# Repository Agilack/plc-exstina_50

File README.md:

# plc-exstina_50
ExStina programmable logic controller

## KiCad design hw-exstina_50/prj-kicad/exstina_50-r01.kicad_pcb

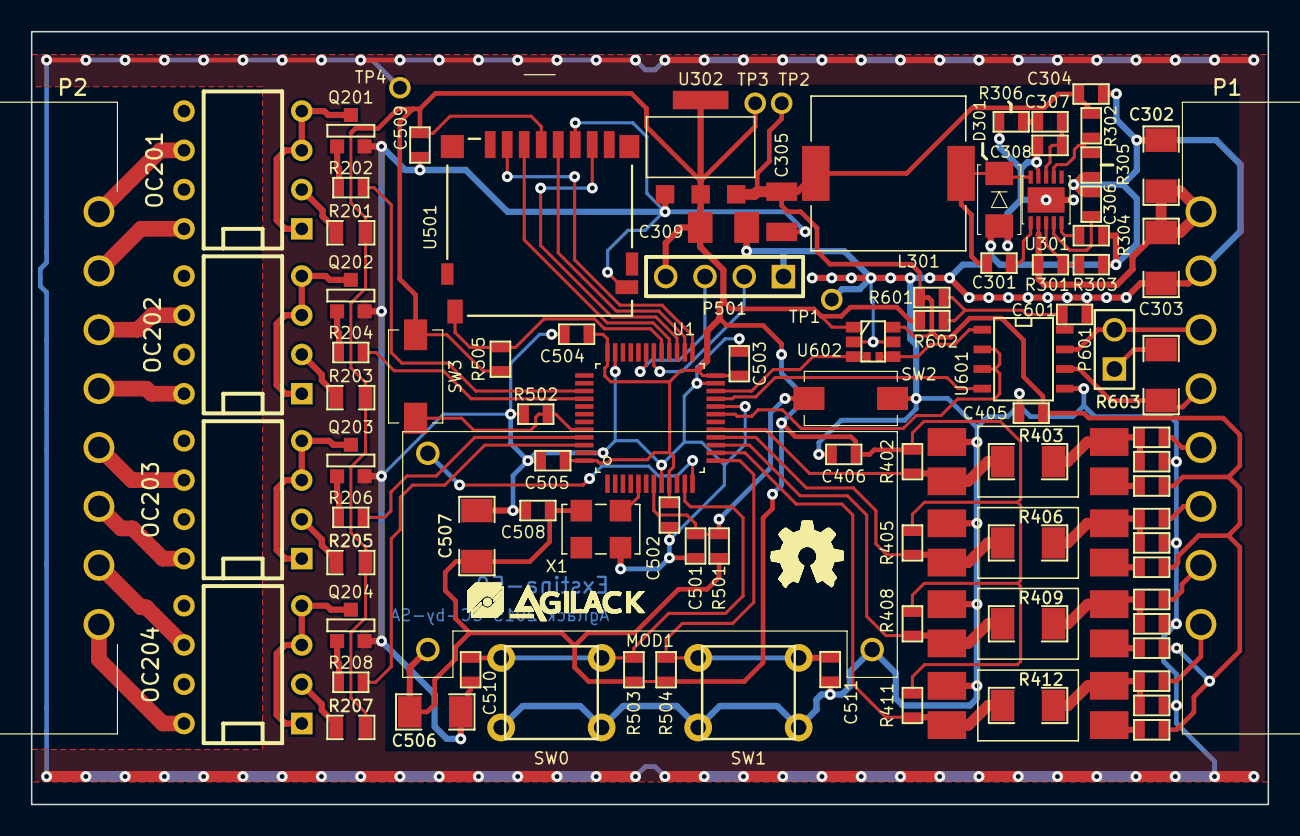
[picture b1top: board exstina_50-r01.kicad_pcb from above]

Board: 2 copper layers, 80.0 x 50.0 mm, 102 parts (0 on the bottom side), 73 nets.

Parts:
C301, C406, C502, C503, C504, C505, C508, C509, C601: 100nF; SMD0603
C302, C303: 10uF; SMD1206
C304, C405, C501, C510, C511: 1uF; SMD0603
C305, C309: 47uF; C_TAJB
C306: 10nF; SMD0603
C307: 180pF; SMD0603
C308: 10Pf; SMD0603
C401, C402, C403, C404: C; SMD0603
C506, C507: 2,2uF; SMD1206
D301: B160; DO214-AC
FB401, FB402, FB403, FB404: FB1000; SMD0603
L301: 47uH; I_MSS1048
MOD1: MOD_DISP
OC201, OC202, OC203, OC204: AQHX213; DIP-8__300
P1, P2: CONN_8; CONN-691701350008B
P501: CONN_4
P601: JUMPER; CONN_2
Q201, Q202, Q203, Q204: T_NPN; SOT23-3
R201, R203, R205, R207: 165; SMD0805
R202, R204, R206, R208, R402, R405, R408, R411, R501, R502, R503, R504, R505: 10k; SMD0603
R301, R304: 100k; SMD0603
R302, R305: R; SMD0603
R303: 48.7k; SMD0603
R306: 75K; SMD0603
R401, R404, R407, R410: 470; SMD0603
R403, R406, R409, R412: 0; SMD1206
R601, R602: 0; SMD0603
R603: 120; SMD1206
R604: 0; SMD0402
SW0, SW1: SW_PUSH; SW_FSM2JH
SW2, SW3: SW_PUSH; SW_434123043816
TP1, TP2, TP3, TP4: CONN_1; TP_PIN
U1: STM32F103CX; LQFP48
U301: TPS54060; SMD_SON10
U302: LDO_1117-3.3; SOT223
U401: VO615; VO615A
U402, U403, U404: OPTO-TRANSISTOR; VO615A
U501: CONN_USD; CONN_114-00841-68
U601: SN65HVD1785; SMD_SO8E
U602: SN74LVC1T45; SOT23-6
X1: 8MHz; Q_SMD5x3
agilack-11.5: 450px; agilack-11.5
ohw_logo: VAL**; ohw-logo

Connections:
+3.3V: C309.1, C406.1, C502.1, C503.1, C504.1, C505.1, C506.1, C507.1, C508.1, C509.1, MOD1.3, P501.4, R201.1, R203.1, R205.1, R207.1, R402.1, R405.1, R408.1, R411.1, R501.2, R503.1, R504.1, R505.1, R602.1, SW3.1, TP3.1, U1.9, U1.24, U1.36, U1.48, U302.2, U302.4, U501.4, U602.1, X1.4
+5V: C304.1, C305.1, C405.1, L301.2, R302.1, R401.2, R404.2, R407.2, R410.2, R601.1, TP2.1, U302.3, U602.6
BOOT: R502.2, SW3.2, U1.44
COMM_1: P1.6, P601.2, U601.7
COMM_2: P1.5, R603.1, U601.6
COMM_IO: U1.19, U601.2, U601.3
DBG_RX: P501.3, U1.31
DBG_TX: P501.2, U1.30
DISP_DAT: MOD1.2, U1.12
EXT-IN-1: FB401.1, P1.4
EXT-IN-2: FB402.1, P1.3
EXT-IN-3: FB403.1, P1.2
EXT-IN-4: FB404.1, P1.1
IN-1: R402.2, R403.2, U1.17, U401.4
IN-2: R405.2, R406.2, U1.16, U402.4
IN-3: R408.2, R409.2, U1.15, U403.4
IN-4: R411.2, R412.2, U1.14, U404.4
MAIN_OSC: U1.5, X1.3
unnamed: OC202.1, OC202.3, OC202.4, Q202.3
unnamed: Q202.1, R204.2
unnamed: OC201.1, OC201.3, OC201.4, Q201.3
unnamed: Q201.1, R202.2
unnamed: OC204.1, OC204.3, OC204.4, Q204.3
unnamed: Q204.1, R208.2
unnamed: OC203.1, OC203.3, OC203.4, Q203.3
unnamed: Q203.1, R206.2
unnamed: OC202.2, R203.2
unnamed: OC203.2, R205.2
unnamed: OC204.2, R207.2
unnamed: OC201.2, R201.2
unnamed: R302.2, R305.1, U301.7
unnamed: C307.1, C308.1, U301.8
unnamed: C307.2, R306.1
unnamed: C301.1, U301.1
unnamed: C301.2, D301.2, L301.1, U301.10
unnamed: R301.2, R303.1, U301.3
unnamed: C306.1, U301.4
unnamed: R304.1, U301.5
unnamed: C404.1, FB404.2, R412.1, U404.2
unnamed: C403.1, FB403.2, R409.1, U403.2
unnamed: R407.1, U403.1
unnamed: R410.1, U404.1
unnamed: C401.1, FB401.2, R403.1, U401.2
unnamed: R401.1, U401.1
unnamed: C402.1, FB402.2, R406.1, U402.2
unnamed: R404.1, U402.1
unnamed: C601.1, R601.2, R602.2, U601.8
unnamed: R604.1, U601.1, U602.4
unnamed: P601.1, R603.2
OUT1: R202.1, U1.39
OUT1-1: OC201.6, P2.1
OUT1-2: OC201.8, P2.2
OUT2: R204.1, U1.40
OUT2-1: OC202.6, P2.3
OUT2-2: OC202.8, P2.4
OUT3: R206.1, U1.45
OUT3-1: OC203.6, P2.5
OUT3-2: OC203.8, P2.6
OUT4: R208.1, U1.46
OUT4-1: OC204.6, P2.7
OUT4-2: OC204.8, P2.8
PWR_V+: C302.1, C303.1, P1.8, R301.1, U301.2
PWR_V-: C302.2, C303.2, C304.2, C305.2, C306.2, C308.2, C309.2, C401.2, C402.2, C403.2, C404.2, C405.2, C406.2, C501.2, C502.2, C503.2, C504.2, C505.2, C506.2, C507.2, C508.2, C509.2, C510.2, C511.2, C601.2, D301.1, MOD1.1, P1.7, P501.1, Q201.2, Q202.2, Q203.2, Q204.2, R303.2, R304.2, R305.2, R306.2, R502.1, SW0.1, SW1.1, SW2.1, TP1.1, TP4.1, U1.8, U1.20, U1.23, U1.35, U1.47, U301.9, U301.PAD, U302.1, U401.3, U402.3, U403.3, U404.3, U501.6, U501.CD1, U601.5, U602.2, U602.5, X1.2
RST: C501.1, R501.1, SW2.2, U1.7
SD_DETECT: R505.2, U1.29, U501.CD2
SPI2_MISO: U1.27, U501.7
SPI2_MOSI: U1.28, U501.3
SPI2_NSS: U1.25, U501.2
SPI2_SCK: U1.26, U501.5
SW0: C510.1, R503.2, SW0.2, U1.11
SW1: C511.1, R504.2, SW1.2, U1.13
UART3_RX: R604.2, U1.22, U602.3
UART3_TX: U1.21, U601.4

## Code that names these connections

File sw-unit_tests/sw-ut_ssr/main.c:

/**
 * Exstina-50 - Outputs unit-test
 *
 * Copyright (c) 2015 Saint-Genest Gwenael <gwen@agilack.fr>
 *
 * This file may be distributed and/or modified under the terms of the
 * GNU General Public License version 2 as published by the Free Software
 * Foundation. (See COPYING.GPL for details.)
 *
 * This file is provided AS IS with NO WARRANTY OF ANY KIND, INCLUDING THE
 * WARRANTY OF DESIGN, MERCHANTABILITY AND FITNESS FOR A PARTICULAR PURPOSE.
 *
 */
#include "hardware.h"
#include "main.h"
#include "uart.h"
#include "display.h"
#include "output.h"

void serial_menu(void);
void disp_menu  (void);
static int but_value(void);

int menu_sel;

int main(void)
{
    int c;

    hw_init();
    uart_init();
    
    hw_out_init();
    
    uart_puts("Exstina-50 - Outputs Unit Test\r\n");
    uart_crlf();
    
    disp_init();
    disp_puts(3, "Outputs Test 0.1");
    
    menu_sel = 0;
    
    while(1)
    {
        serial_menu();
        disp_menu();
        while ( ( ! uart_isready()) && (but_value() == 0) )
            ;
        
        if (but_value() != 0)
        {
            /* If left button has been pressed */
            if (but_value() & 2)
            {
                menu_sel++;
                if (menu_sel == 5)
                    menu_sel = 1;
            }
            /* If right button has been pressed  */
            else if (but_value() & 8)
            {
                switch(menu_sel)
                {
                    case 1:
                        out_toggle(OUT_1);
                        break;
                    case 2:
                        out_toggle(OUT_2);
                        break;
                    case 3:
                        out_toggle(OUT_3);
                        break;
                    case 4:
                        out_toggle(OUT_4);
                        break;
                }
            }
            /* Wait until all button released */
            while( but_value() )
                ;
            continue;
        }
        
        c = uart_rd();
        switch(c)
        {
            case 'a':
                uart_puts("Set ALL SSR ON\r\n");
                out_set(OUT_1, OUT_ON);
                out_set(OUT_2, OUT_ON);
                out_set(OUT_3, OUT_ON);
                out_set(OUT_4, OUT_ON);
                break;
                
            case 'n':
                uart_puts("Set ALL SSR OFF\r\n");
                out_set(OUT_1, OUT_OFF);
                out_set(OUT_2, OUT_OFF);
                out_set(OUT_3, OUT_OFF);
                out_set(OUT_4, OUT_OFF);
                break;
                
            case '1':
                uart_puts("Set SSR-1 ");
                /* Invert the output 1 state */
                out_toggle(OUT_1);
                /* Send new state to debug port */
                if (out_status(OUT_1) == OUT_ON)
                    uart_puts("ON\r\n");
                else
                    uart_puts("OFF\r\n");
                break;
                
            case '2':
                uart_puts("Set SSR-2 ");
                /* Invert the output 2 state */
                out_toggle(OUT_2);
                /* Send new state to debug port */
                if (out_status(OUT_2) == OUT_ON)
                    uart_puts("ON\r\n");
                else
                    uart_puts("OFF\r\n");
                break;
                
            case '3':
                uart_puts("Set SSR-3 ");
                /* Invert the output 3 state */
                out_toggle(OUT_3);
                /* Send new state to debug port */
                if (out_status(OUT_3) == OUT_ON)
                    uart_puts("ON\r\n");
                else
                    uart_puts("OFF\r\n");
                break;
                
            case '4':
                uart_puts("Set SSR-4 ");
                /* Invert the output 4 state */
                out_toggle(OUT_4);
                /* Send new state to debug port */
                if (out_status(OUT_4) == OUT_ON)
                    uart_puts("ON\r\n");
                else
                    uart_puts("OFF\r\n");
                break;
                
            default:
                uart_puts("Unknown command\r\n");
        }
    }
}

void serial_menu(void)
{
    uart_puts("Use this kays to control relays :\r\n");
    uart_puts(" '1' : toggle the state of Relay 1\r\n");
    uart_puts(" '2' : toggle the state of Relay 2\r\n");
    uart_puts(" '3' : toggle the state of Relay 3\r\n");
    uart_puts(" '4' : toggle the state of Relay 4\r\n");
    uart_puts(" 'a' : set all to ON\r\n");
    uart_puts(" 'n' : set all to OFF\r\n");
    uart_puts("\r\n >");
}

void disp_menu(void)
{
    char str_labels[17];
    char str_state[17];
    int oval;
    
    /* Insert output-1 label */
    if (menu_sel == 1) strcpy(str_labels +  0, "OUT1");
    else               strcpy(str_labels +  0, " O1 ");
    /* Insert output-2 label */
    if (menu_sel == 2) strcpy(str_labels +  4, "OUT2");
    else               strcpy(str_labels +  4, " O2 ");
    /* Insert output-3 label */
    if (menu_sel == 3) strcpy(str_labels +  8, "OUT3");
    else               strcpy(str_labels +  8, " O3 ");
    /* Insert output-4 label */
    if (menu_sel == 4) strcpy(str_labels + 12, "OUT4");
    else               strcpy(str_labels + 12, " O4 ");

    /* Insert output-1 value */
    oval = out_status(OUT_1);
    if (oval) strcpy(str_state +  0, " ON ");
    else      strcpy(str_state +  0, " -- ");
    /* Insert output-2 value */
    oval = out_status(OUT_2);
    if (oval) strcpy(str_state +  4, " ON ");
    else      strcpy(str_state +  4, " -- ");
    /* Insert output-3 value */
    oval = out_status(OUT_3);
    if (oval) strcpy(str_state +  8, " ON ");
    else      strcpy(str_state +  8, " -- ");
    /* Insert output-4 value */
    oval = out_status(OUT_4);
    if (oval) strcpy(str_state + 12, " ON ");
    else      strcpy(str_state + 12, " -- ");
    
    /* Update the labels line on display */
    disp_puts(1, str_labels);
    disp_puts(0, str_state);
}

static int but_value(void)
{
    int v;
    v  = reg_rd(GPIO_IDR(GPIOA));
    v &= 0x0A;
    v ^= 0x0A;
    return v;
}

char *strcpy(char *dest, const char *src)
{
    char *dsave = dest;
        while(*src)
        {
                *dest = *src;
                src++;
                dest++;
        }
        *dest = 0;
        return dsave;
}
/* EOF */

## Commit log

2015-07-17 = ADD: Kicad project for exstina-50 board rev 1
2015-07-21 = ADD: Production files for board rev 1
2015-09-21 = ADD: Unit test firmware for outputs (relays)
2015-09-22 = ADD: Unit test for display plugin module
2015-09-23 = ADD: Unit test for SD-card interface (SPI)
2015-10-21 = UPD: Improve display unit-test
2015-10-22 = UPD: Show "SSR" unit-test name on display
2015-10-23 = UPD: Add standalone control of SSR unit-test (using display and buttons)
2015-10-26 = UPD: Move outputs manipulation to re-usable hi-level functions Fix bug with the default state of out-2
2016-06-07 = ADD: schematics library was missing in previous commits

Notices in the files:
hw-exstina_50/prj-kicad/exstina_50-r01.kicad_pcb:
Agilack 2015 CC-by-SA
